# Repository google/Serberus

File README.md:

<h1 align="center">
  <br>
    <a>SERBERUS</a>
</h1>

<h4 align="center">Multi-headed and Multi-Protocol embedded system hacking tool.</h4>

<p align="center">
  
  <br>
</p>

# OVERVIEW
- Note: This is not an officially supported Google product
- The Serberus is a serial Man-in-the-Middle hardware hacking tool
- It has 4 channels, based on the FTDI 4233
- Has the ability to connect to JTAG, SPI, I2C and SWD interfaces
- Has a Level shifter and switch to allow you to connect to logic voltages of 1.8, 2.5 and 3.3v or any arbitrary voltage between 1.65v and 5.5v

# BOARD RENDERING 

<p align="center">
  
  <br>
</p>

# CONTENTS
- [System Requirements](#system-requirements)
- [What makes the Serberus unique](#what-makes-the-serberus-unique)
- [Basic Usage](#basic-usage)
  - [UARTS](#uarts)
  - [JTAG](#jtag)
  - [Other Connections](#swd-i2c-spi)
- [Switch 1](#switch-1)
- [Switch 2](#switch-2)
- [Jumpers](#jumpers-j8-and-j9)
  - [J8](#j8)
  - [J9](#j9)
- [UART]()
- [JTAG]()
- [SPI]()
- [I2C]()
- [Cortex](#cortex)
- [Logic Analyzer](#logic-analyzer)
- [Power Delivery](#power-delivery)
- [License](#license)

## System Requirements
No drivers should be required, the FTDI devices are supported by most operating systems.
The UART ports will work right away with screen, putty or your favorite serial console or serial access application such as OPENOCD.
## What makes the Serberus unique:
The Serberus is based on a couple of earlier FTDI USB to TTL tools, the TIMEP and the TIGARD. The items below are some of the major changes from those designs.
- 3 UART Ports
- J-Link Compatible JTAG connector - use any of those J-link to XXX connectors or breakouts
- Indicators for each of the 4 serial channels - help debugging
- 2.54 MM Logic Analyzer connector - Easily connect the most common logic analyzers or an MSO scope
## Basic Usage
When you plug in the Serberus, your system will be recognize the FTDI chip and the 4 serial ports. 
### UARTS
The first, third and forth serial ports are intended for UART. You can use your favorite serial access tool, (Putty, screen) to access them as you would any other USB to serial device
<br>
example<br>
`screen /dev/ttyUSB0 {baudrate}`

### JTAG
I need to do a little more work here as most of the tools like `pyftdi` and `flashrom` do not look for the FT4233. `pyftdi` should work with `--vidpid` flag and the value 0403:6041. You need to change udev permissions.
For OpenOCD, compile from source using "./configure --enable-ftdi". USB VID:PID is 0403:6041.

### SWD, I2C, SPI
Details coming soon

## SWITCH 1
Switch 1 is the rotary target voltage select switch, it has 4 positions. The first position is intended to match the voltage of your target and should rarely be needed, however it is included for those one-off scenarios where your target has a strange voltage between 1v6 and 5v5 but will not work with the provided levels. It will also adapt if your target changes voltage during the power up process. (I encountered this only once in all my years of testing.) J9 must have a jumper on it to make this connection.

The remaining 3 positions match the likely voltages of 1v8, 3v3 and 5v. Ideally in your workflow you will test your target and know what voltage level is appropriate. This switch works by taking the output of the voltage regulators U1, U2 or the 5v VBUS voltage and sending it to the level shifters VREF pin, to match the logic level of these signals.

| Position | Function |
|----------|----------|
| 1        | VTARGET  |
| 2        | 1v8      | 
| 3        | 3v3      |
| 4        | 5v       |

## SWITCH 2
Switch 2 is for combining various inputs to allow the second serial port to be used for JTAG, SPI, SWD and I2C. Switch to the left is for JTAG and SPI, separating the necessary TX and RX pins while the right position combines them for SWD and I2C.

## Jumpers J8 and J9
### J8 
connect VREF to VTARGET, allowing you to take the voltage level of your target and use that as the voltage level of the level shifters. J8 must have a jumper in place and SW1 must be in the first position for this feature to function.
### J9
For iCE FPGA programming, I added this feature from the TIGARD as it was an easy feature to include for a minimal cost. Close the jumper to connect UARTA_RX and Misc_RX, make sure SW2 is in JTAG mode. 

## UART
The top connector has 3 UART connections, it is a standard 20 pin flat cable connector. The first UART has all 7 signal pins connected, for those rare instances where they are needed. The first UART is mapped to the first 4233 channel.
<br>
The second and third UARTS are mapped to the 3rd and 4th channels ports, as the second is used by the combined JTAG/SWD/I2C and SPI port. These ports only have TX and RX connected.

### UART Header Pinout

| Pin   | Function  |
|-------|-----------|
| 1     | VTARGET   |
| 2     | VTARGET   | 
| 3     | GND       |
| 4     | TX-C      |
| 5     | TX-A      |
| 6     | RX-C      |
| 7     | RX-A      |
| 8     | GND       |
| 9     | RTS-A     |
| 10    | NC        |
| 11    | CTS-A     |
| 12    | RX-D      |
| 13    | DTR-A     |
| 14    | VTARGET   |
| 15    | DSR-A     |
| 16    | TX-D      |
| 17    | DCD-A     |
| 18    | RX-D      |
| 19    | NC        |
| 20    | GND       |

## JTAG
The JTAG header is presented on J3, the right side of the board opposite the USB connector. The connector is a 20 Pin standard pitch Flat cable style.  It is intended to match the Segger J-LINK pinout as much as possible, making it easier to use the many J-Link connectors to make a direct connection to an accessible header on your target.

### JTAG Header Pinout

| Pin   | Function |
|-------|----------|
| 1     | VTARGET  |
| 2     | NC       |
| 3     | TRST     |
| 4     | GND      |
| 5     | TDI      |
| 6     | GND      |
| 7     | TMS      |
| 8     | GND      |
| 9     | TCK      |
| 10    | GND      |
| 11    | MISC_RX* |
| 12    | GND      | 
| 13    | TDO      | 
| 14    | GND      |
| 15    | SRST     |
| 16    | GND      |
| 17    | NC       |
| 18    | GND      |
| 19    | NC       |
| 20    | GND      |

*Connected to BDBUS 6 as an input on the FT4233, only needed for bizarre on-off connections, for most purposes, leave as NC.

## SPI
 SW2 in _leftmost_ position (1)
### SPI Pinout:
| Pin   | Function      |
|-------|---------------|
| 1     | CS            |
| 2     | VTARGET       |
| 3     | CIPO/MISO     |
| 4     | WP (PULLUP)   |
| 5     | EN (PULLUP)   |
| 6     | CLK           |
| 7     | GND           |
| 8     | COPI/MOSI     |

## I2C
 SW2 in _rightmost_ position (2)
### I2C Pinout:
| Pin   | Function |
|-------|----------|
| 1     | SCL      |
| 2     | SDA      |
| 3     | VTARGET  |
| 4     | GND      |

## CORTEX
A 10 pin cortex debug connector is present and will enable an easy connection to this common debug connector. 
### CORTEX Pinout
| Pin   | Function     |
|-------|--------------|
| 1     | VTARGET      |
| 2     | CORTEX PIN 2 |
| 3     | GND          |
| 4     | TCK          |
| 5     | GND          |
| 6     | TDO          |
| 7     | NC           |
| 8     | TDI          |
| 9     | GND          |
| 10    | SRST         |

## Logic Analyzer
The 14 pin header at the bottom next to the SPI and I2C connectors replicates most of the signal lines for easy connection to a logic analyzer or digital MSO lines of an oscilloscope. The pin header is standard 2.54mm pitch to easily connect using standard Dupont style jumper wires.
### Logic Analyzer Pinout

| Pin   | Function      |
|-------|---------------|
| 1     | CLK           |
| 2     | COPI/TDI      | 
| 3     | CIPO/TDO/SWDIO|
| 4     | TMS/CS        |
| 5     | TRST          |
| 6     | SRST          |
| 7     | TX-A          |
| 8     | RX-A          |
| 9     | TX-C          |
| 10    | RX-C          |
| 11    | TX-D          |
| 12    | RX-D          |
| 13    | GND           |
| 14    | GND           |

## POWER DELIVERY
The FT4233 is capable of power delivery (PD) and the design includes a DPO2036 for OVP. No other PD features have been added and the FTDI settings are at default. Power delivery is something that could be added but is well beyond the scope of this device for its initial release. Please feel free to experiment with forked designs.

## License
```Copyright 2024 Google LLC
Licensed under the Apache License, Version 2.0 (the "License");
you may not use this file except in compliance with the License.
You may obtain a copy of the License at

    https://www.apache.org/licenses/LICENSE-2.0

Unless required by applicable law or agreed to in writing, software
distributed under the License is distributed on an "AS IS" BASIS,
WITHOUT WARRANTIES OR CONDITIONS OF ANY KIND, either express or implied.
See the License for the specific language governing permissions and
limitations under the License.
```

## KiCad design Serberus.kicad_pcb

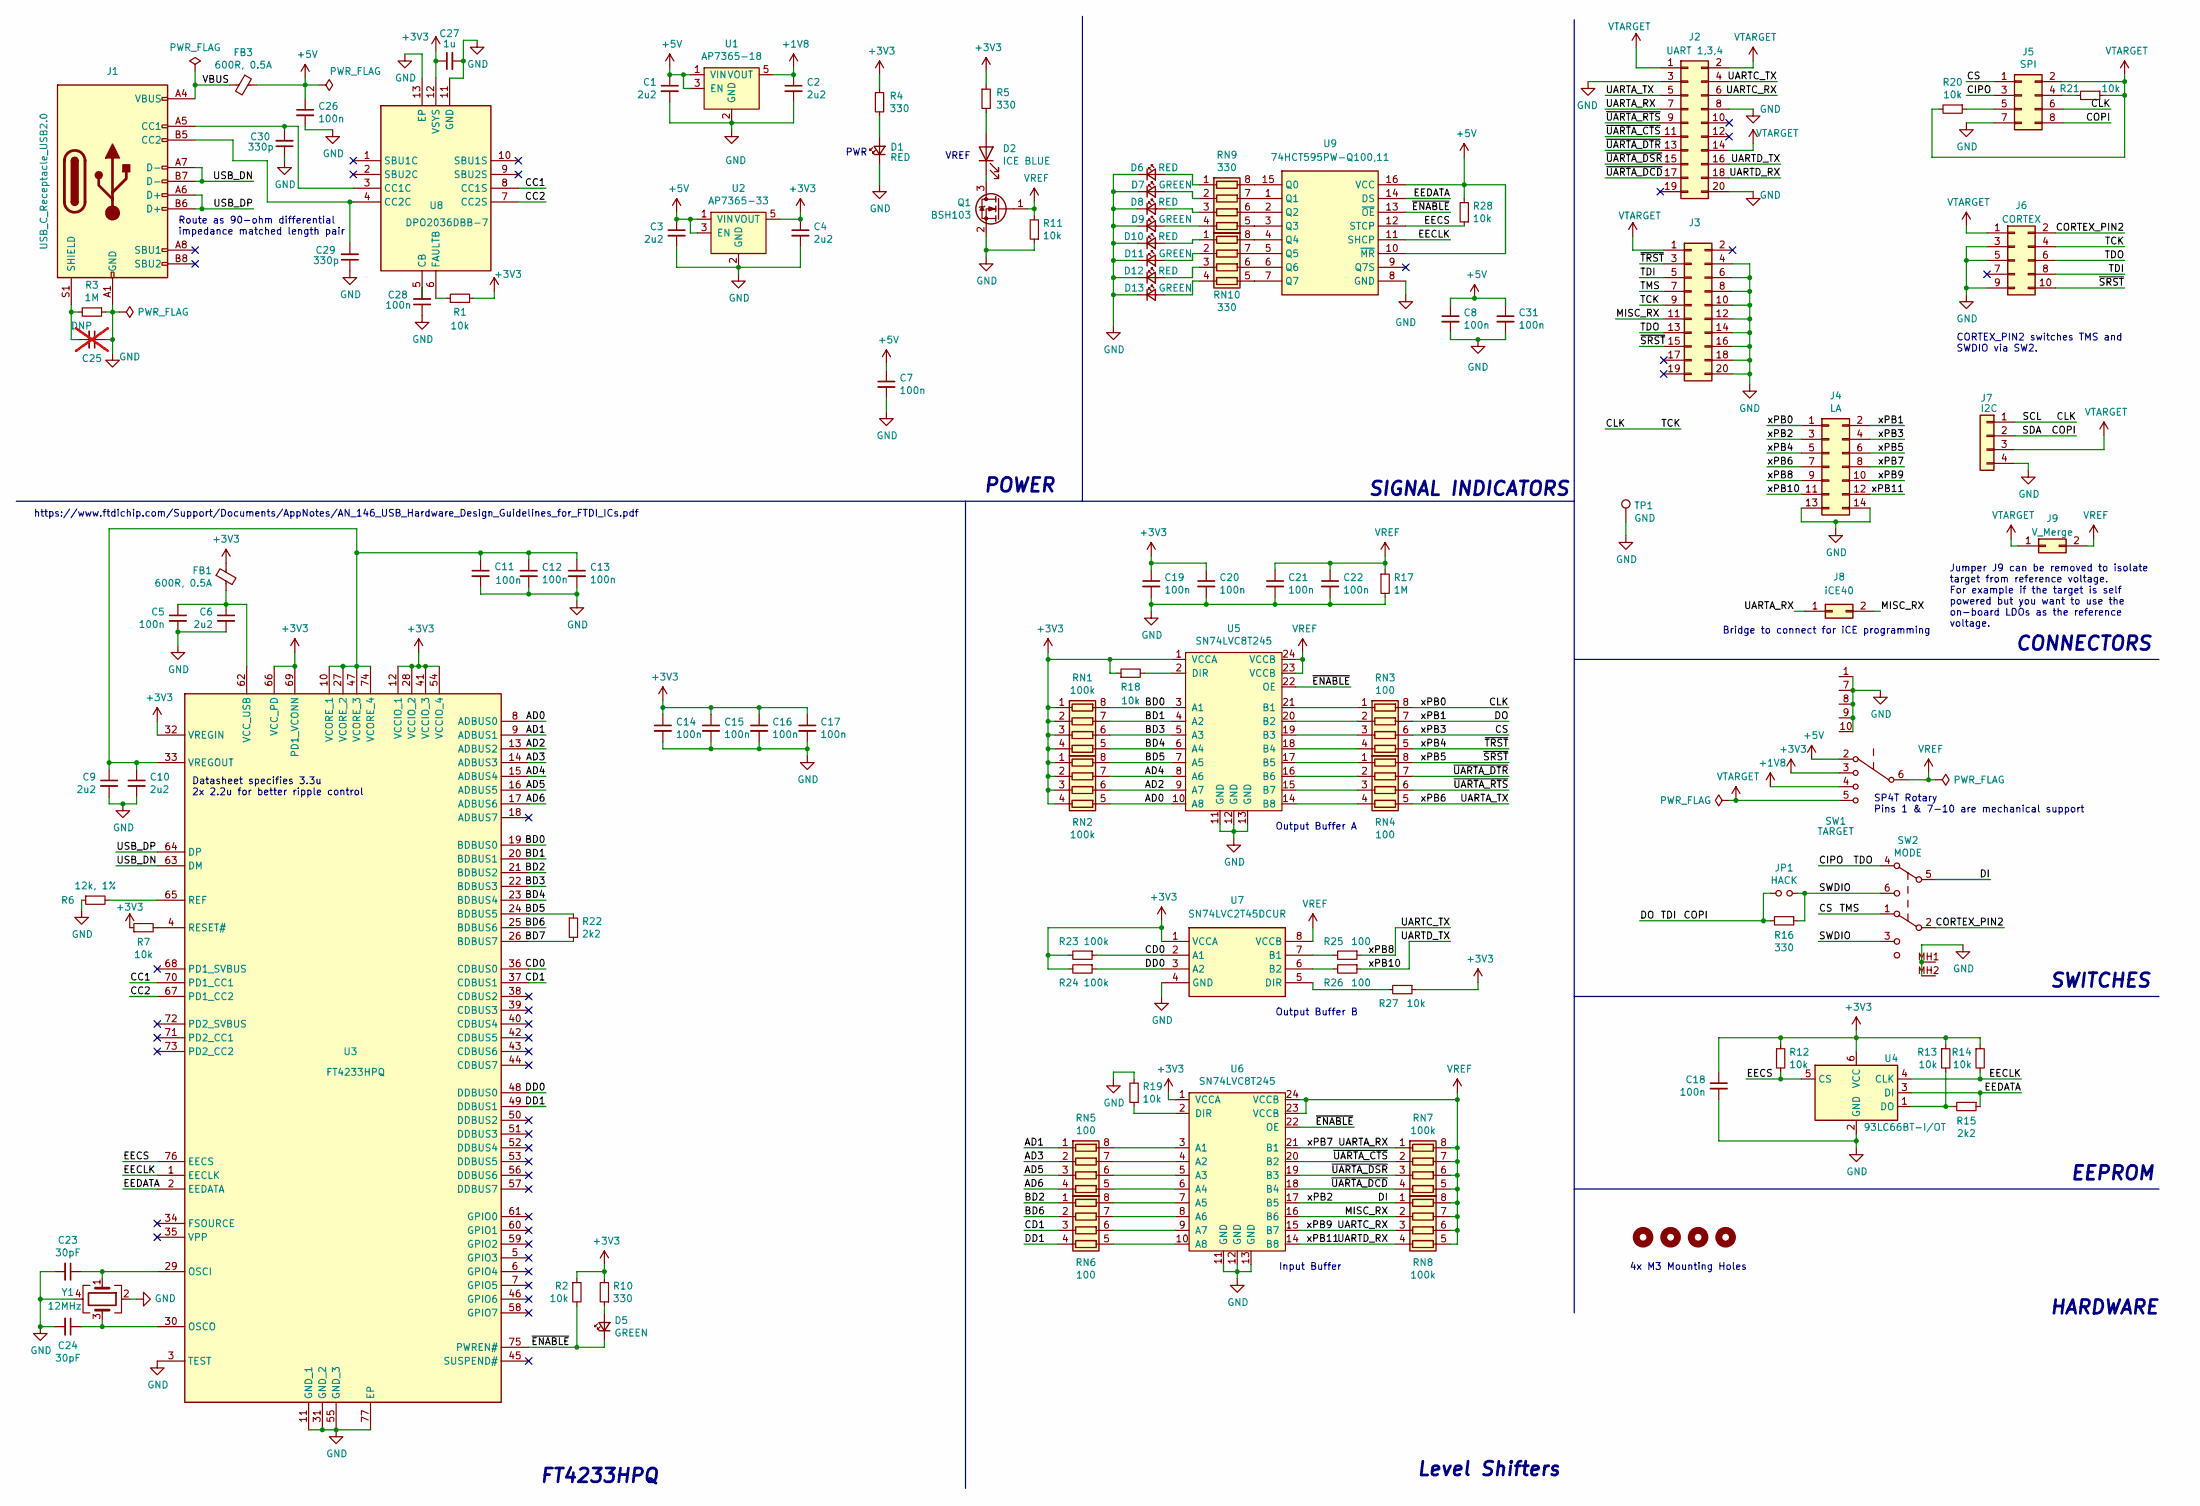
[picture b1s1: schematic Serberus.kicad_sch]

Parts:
C1, C2, C3, C4, C6, C9, C10: 2u2; C_0402_1005Metric; LCSC C307419
C5, C7, C8, C11, C12, C13, C14, C15, C16, C17, C18, C19, C20, C21, C22, C26, C28, C31: 100n; C_0402_1005Metric; LCSC C100072
C23, C24: 30pF; C_0402_1005Metric; LCSC C159804
C25: DNP; C_0402_1005Metric; not fitted
C27: 1u; C_0402_1005Metric; LCSC C52923
C29, C30: 330p; C_0402_1005Metric; LCSC C307432
D1, D6, D8, D10, D12: RED; LED_0603_1608Metric; LCSC C157741
D2: ICE BLUE; LED_0603_1608Metric; LCSC C389522
D5, D7, D9, D11, D13: GREEN; LED_0603_1608Metric; LCSC C12065
FB1, FB3: 600R, 0.5A; L_0402_1005Metric; LCSC C76886
H1, H2, H3, H4: MountingHole; MountingHole_3.2mm_M3_ISO7380
J1: USB_C_Receptacle_USB2.0; USB_C_Receptacle_HRO_TYPE-C-31-M-12; LCSC C165948
J2: UART 1,3,4; RHDRRA20W64P254_2X10_3306X885X910P; Mouser Part Number 571-5103311-5
J3: SWD/JTAG2; RHDRRA20W64P254_2X10_3306X885X910P; Mouser Part Number 571-5103311-5
J4: LA; PinHeader_2x07_P2.54mm_Vertical; LCSC C5156678
J5: SPI; PinHeader_2x04_P2.54mm_Vertical; LCSC C492421
J6: CORTEX; PinHeader_2x05_P1.27mm_Vertical_SMD; LCSC C448647
J7: I2C; PinHeader_1x04_P2.54mm_Vertical; LCSC C2691448
J8: iCE40; PinHeader_1x02_P2.54mm_Vertical; LCSC C492401
J9: V_Merge; PinHeader_1x02_P2.54mm_Vertical; LCSC C492401
JP1: HACK; SolderJumper-2_P1.3mm_Open_RoundedPad1.0x1.5mm
Q1: BSH103; SOT-23_RoundRect; LCSC C88711
R1, R2, R7, R11, R12, R13, R14, R18, R19, R20, R21, R27, R28: 10k; R_0402_1005Metric; LCSC C25744
R3, R17: 1M; R_0402_1005Metric; LCSC C26087
R4, R5, R10, R16: 330; R_0402_1005Metric; LCSC C25104
R6: 12k, 1%; R_0402_1005Metric; LCSC C25752
R15, R22: 2k2; R_0402_1005Metric; LCSC C25879
R23, R24: 100k; R_0402_1005Metric; LCSC C25741
R25: 100; R_0402_1005Metric; LCSC C25076
R26: 100; R_0402_1005Metric; LCSC C25879
RN1, RN2, RN7, RN8: 100k; R_Array_Convex_4x0402_RoundRect; LCSC C25724
RN3, RN4, RN5, RN6: 100; R_Array_Convex_4x0402_RoundRect; LCSC C48442
RN9, RN10: 330; R_Array_Convex_4x0402_RoundRect; LCSC C43557
SW1: TARGET; NR01105ANG132A; Manufacturer_Part_Number NR01105ANG13-2A; Mouser Part Number 633-NR01105ANG13-2A
SW2: MODE; SSSF021500; Mouser Part Number 688-SSSF021500
TP1: GND; TestPoint_Keystone_5000-5004_Miniature; LCSC C238122
U1: AP7365-18; SOT-23-5_RoundRect; LCSC C460402
U2: AP7365-33; SOT-23-5_RoundRect; LCSC C150742
U3: FT4233HPQ; QFN40P900X900X100-77N-D; Mouser Part Number 895-FT4233HPQ-TRAY
U4: 93LC66BT-I/OT; SOT-23-6_RoundRect; LCSC C2061454
U5, U6: SN74LVC8T245; TSSOP-24_4.4x7.8mm_P0.65mm; LCSC C27643
U7: SN74LVC2T45DCUR; SOP50P310X90-8N; Mouser Part Number 595-SN74LVC2T45DCUR
U8: DPO2036DBB-7; QFN45P200X200X65-13N; Mouser Part Number 621-DPO2036DBB-7
U9: 74HCT595PW-Q100,11; SOP65P640X110-16N; Mouser Part Number 771-74HCT595PWQ10011
Y1: 12MHz; Crystal_SMD_3225-4Pin_3.2x2.5mm_RoundRect; LCSC C9002

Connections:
+1V8: C2.1, SW1.4, U1.5 (VOUT)
+3V3: C4.1, C14.1, C15.1, C16.1, C17.1, C18.1, C19.1, C20.1, C27.1, FB1.1, R1.2, R2.1, R4.1, R5.1, R7.1, R10.2, R12.1, R13.1, R14.1, R18.1, R23.2, R24.2, R27.1, RN1.1 (R1.1), RN1.2 (R2.1), RN1.3 (R3.1), RN1.4 (R4.1), RN2.1 (R1.1), RN2.2 (R2.1), RN2.3 (R3.1), RN2.4 (R4.1), SW1.3, U2.5 (VOUT), U3.12 (VCCIO_1), U3.28 (VCCIO_2), U3.32 (VREGIN), U3.41 (VCCIO_3), U3.54 (VCCIO_4), U3.66 (VCC_PD), U3.69 (PD1_VCONN), U4.6 (VCC), U5.1 (VCCA), U6.1 (VCCA), U7.1 (VCCA), U8.12 (VSYS)
+5V: C1.1, C3.1, C7.1, C8.1, C26.1, C31.1, FB3.1, R28.2, SW1.2, U1.1 (VIN), U1.3 (EN), U2.1 (VIN), U2.3 (EN), U9.10 (~MR), U9.16 (VCC)
/AD0: RN2.5 (R4.2), U3.8 (ADBUS0), U5.10 (A8)
/AD1: RN5.1 (R1.1), U3.9 (ADBUS1)
/AD2: RN2.6 (R3.2), U3.13 (ADBUS2), U5.9 (A7)
/AD3: RN5.2 (R2.1), U3.14 (ADBUS3)
/AD4: RN2.7 (R2.2), U3.15 (ADBUS4), U5.8 (A6)
/AD5: RN5.3 (R3.1), U3.16 (ADBUS5)
/AD6: RN5.4 (R4.1), U3.17 (ADBUS6)
/BD0: RN1.8 (R1.2), U3.19 (BDBUS0), U5.3 (A1)
/BD1: RN1.7 (R2.2), U3.20 (BDBUS1), U5.4 (A2)
/BD2: RN6.1 (R1.1), U3.21 (BDBUS2)
/BD3: RN1.6 (R3.2), U3.22 (BDBUS3), U5.5 (A3)
/BD4: RN1.5 (R4.2), U3.23 (BDBUS4), U5.6 (A4)
/BD5: R22.1, RN2.8 (R1.2), U3.24 (BDBUS5), U5.7 (A5)
/BD6: RN6.2 (R2.1), U3.25 (BDBUS6)
/BD7: R22.2, U3.26 (BDBUS7)
/CC1: U3.70 (PD1_CC1), U8.8 (CC1S)
/CC2: U3.67 (PD1_CC2), U8.7 (CC2S)
/CD0: R23.1, U3.36 (CDBUS0), U7.2 (A1)
/CD1: RN6.3 (R3.1), U3.37 (CDBUS1)
/CIPO: J3.13, J5.3, J6.6, SW2.4
/CLK: J3.9, J4.1, J5.6, J6.4, J7.1, RN3.8 (R1.2)
/COPI: J3.5, J4.2, J5.8, J6.8, J7.2, JP1.1, R16.2, RN3.7 (R2.2)
/CORTEX_PIN2: J6.2, SW2.2
/CS: J3.7, J4.4, J5.1, RN3.6 (R3.2), SW2.1
/DD0: R24.1, U3.48 (DDBUS0), U7.3 (A2)
/DD1: RN6.4 (R4.1), U3.49 (DDBUS1)
/DI: J4.3, RN8.1 (R1.1), SW2.5, U6.17 (B5)
/EECLK: R14.2, U3.1 (EECLK), U4.4 (CLK), U9.11 (SHCP)
/EECS: R12.2, R28.1, U3.76 (EECS), U4.5 (CS), U9.12 (STCP)
/EEDATA: R15.1, U3.2 (EEDATA), U4.3 (DI), U9.14 (DS)
/MISC_RX: J3.11, J8.2, RN8.2 (R2.1), U6.16 (B6)
/SWDIO: JP1.2, R16.1, SW2.3, SW2.6
/UARTA_RX: J2.7, J4.8, J8.1, RN7.1 (R1.1), U6.21 (B1)
/UARTA_TX: J2.5, J4.7, RN4.5 (R4.2)
/UARTC_RX: J2.6, J4.10, RN8.3 (R3.1), U6.15 (B7)
/UARTC_TX: J2.4, J4.9, R25.1
/UARTD_RX: J2.18, J4.12, RN8.4 (R4.1), U6.14 (B8)
/UARTD_TX: J2.16, J4.11, R26.1
/USB_DN: J1.A7 (D-), J1.B7 (D-), U3.63 (DM)
/USB_DP: J1.A6 (D+), J1.B6 (D+), U3.64 (DP)
/VBUS: FB3.2, J1.A4 (VBUS), J1.A9 (VBUS), J1.B4 (VBUS), J1.B9 (VBUS)
/xPB4: J3.3, J4.5, RN3.5 (R4.2)
/xPB5: J3.15, J4.6, J6.10, RN4.8 (R1.2)
/~ENABLE: D5.1 (K), R2.2, U3.75 (PWREN#), U5.22 (OE), U6.22 (OE), U9.13 (~OE)
/~UARTA_CTS: J2.11, RN7.2 (R2.1), U6.20 (B2)
/~UARTA_DCD: J2.17, RN7.4 (R4.1), U6.18 (B4)
/~UARTA_DSR: J2.15, RN7.3 (R3.1), U6.19 (B3)
/~UARTA_DTR: J2.13, RN4.7 (R2.2)
/~UARTA_RTS: J2.9, RN4.6 (R3.2)
GND: C1.2, C2.2, C3.2, C4.2, C5.2, C6.2, C7.2, C8.2, C9.2, C10.2, C11.2, C12.2, C13.2, C14.2, C15.2, C16.2, C17.2, C18.2, C19.2, C20.2, C21.2, C22.2, C23.2, C24.2, C25.1, C26.2, C27.2, C28.1, C29.1, C30.1, C31.2, D1.1 (K), D6.1 (K), D7.1 (K), D8.1 (K), D9.1 (K), D10.1 (K), D11.1 (K), D12.1 (K), D13.1 (K), J1.A1 (GND), J1.A12 (GND), J1.B1 (GND), J1.B12 (GND), J2.3, J2.8, J2.20, J3.4, J3.6, J3.8, J3.10, J3.12, J3.14, J3.16, J3.18, J3.20, J4.13, J4.14, J5.7, J6.3, J6.5, J6.9, J7.4, Q1.2 (S), R3.1, R6.1, R11.1, R17.2, R19.2, SW1.1 (1_Support), SW1.7 (7_Support), SW1.8 (8_Support), SW1.9 (9_Support), SW1.10 (10_Support), SW2.MH1, SW2.MH2, TP1.1, U1.2 (GND), U2.2 (GND), U3.3 (TEST), U3.11 (GND_1), U3.31 (GND_2), U3.55 (GND_3), U3.77 (EP), U4.2 (GND), U5.11 (GND), U5.12 (GND), U5.13 (GND), U6.11 (GND), U6.12 (GND), U6.13 (GND), U7.4 (GND), U8.11 (GND), U8.13 (EP), U9.8 (GND), Y1.2, Y1.4
unnamed: D1.2 (A), R4.2
unnamed: D2.2 (A), R5.2
unnamed: D2.1 (K), Q1.3 (D)
unnamed: D5.2 (A), R10.1
unnamed: D6.2 (A), RN9.1 (R1.1)
unnamed: D7.2 (A), RN9.2 (R2.1)
unnamed: D8.2 (A), RN9.3 (R3.1)
unnamed: D9.2 (A), RN9.4 (R4.1)
unnamed: D10.2 (A), RN10.1 (R1.1)
unnamed: D11.2 (A), RN10.2 (R2.1)
unnamed: D12.2 (A), RN10.3 (R3.1)
unnamed: D13.2 (A), RN10.4 (R4.1)
unnamed: C30.2, J1.A5 (CC1), U8.3 (CC1C)
unnamed: C29.2, J1.B5 (CC2), U8.4 (CC2C)
unnamed: C25.2, J1.S1 (SHIELD), R3.2
unnamed: J5.4, R21.2
unnamed: J5.5, R20.1
unnamed: RN3.1 (R1.1), U5.21 (B1)
unnamed: RN3.2 (R2.1), U5.20 (B2)
unnamed: RN3.3 (R3.1), U5.19 (B3)
unnamed: RN3.4 (R4.1), U5.18 (B4)
unnamed: RN4.1 (R1.1), U5.17 (B5)
unnamed: RN4.2 (R2.1), U5.16 (B6)
unnamed: RN4.3 (R3.1), U5.15 (B7)
unnamed: RN4.4 (R4.1), U5.14 (B8)
unnamed: RN5.8 (R1.2), U6.3 (A1)
unnamed: RN5.7 (R2.2), U6.4 (A2)
unnamed: RN5.6 (R3.2), U6.5 (A3)
unnamed: RN5.5 (R4.2), U6.6 (A4)
unnamed: RN6.8 (R1.2), U6.7 (A5)
unnamed: RN6.7 (R2.2), U6.8 (A6)
unnamed: RN6.6 (R3.2), U6.9 (A7)
unnamed: RN6.5 (R4.2), U6.10 (A8)
unnamed: RN9.8 (R1.2), U9.15 (Q0)
unnamed: RN9.7 (R2.2), U9.1 (Q1)
unnamed: RN9.6 (R3.2), U9.2 (Q2)
unnamed: RN9.5 (R4.2), U9.3 (Q3)
unnamed: RN10.8 (R1.2), U9.4 (Q4)
unnamed: RN10.7 (R2.2), U9.5 (Q5)
unnamed: RN10.6 (R3.2), U9.6 (Q6)
unnamed: RN10.5 (R4.2), U9.7 (Q7)
unnamed: C23.1, U3.29 (OSCI), Y1.1
unnamed: C24.1, U3.30 (OSCO), Y1.3
unnamed: R6.2, U3.65 (REF)
unnamed: R7.2, U3.4 (RESET#)
unnamed: C5.1, C6.1, FB1.2, U3.62 (VCC_USB)
unnamed: C9.1, C10.1, C11.1, C12.1, C13.1, U3.10 (VCORE_1), U3.27 (VCORE_2), U3.33 (VREGOUT), U3.47 (VCORE_3), U3.74 (VCORE_4)
unnamed: R13.2, R15.2, U4.1 (DO)
unnamed: R18.2, U5.2 (DIR)
unnamed: R19.1, U6.2 (DIR)
unnamed: R25.2, U7.7 (B1)
unnamed: R26.2, U7.6 (B2)
unnamed: R27.2, U7.5 (DIR)
unnamed: C28.2, U8.5 (CB)
unnamed: R1.1, U8.6 (FAULTB)
VREF: C21.1, C22.1, J9.2, Q1.1 (G), R11.2, R17.1, RN7.5 (R4.2), RN7.6 (R3.2), RN7.7 (R2.2), RN7.8 (R1.2), RN8.5 (R4.2), RN8.6 (R3.2), RN8.7 (R2.2), RN8.8 (R1.2), SW1.6 (Common), U5.23 (VCCB), U5.24 (VCCB), U6.23 (VCCB), U6.24 (VCCB), U7.8 (VCCB)
VTARGET: J2.1, J2.2, J2.14, J3.1, J5.2, J6.1, J7.3, J9.1, R20.2, R21.1, SW1.5

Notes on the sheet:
Datasheet specifies 3.3u 2x 2.2u for better ripple control
SWITCHES
EEPROM
SIGNAL INDICATORS
Route as 90-ohm differential impedance matched length pair
Level Shifters
VREF
FT4233HPQ
HARDWARE
Output Buffer B
https://www.ftdichip.com/Support/Documents/AppNotes/AN_146_USB_Hardware_Design_Guidelines_for_FTDI_ICs.pdf
Output Buffer A
SP4T Rotary Pins 1 & 7-10 are mechanical support
4x M3 Mounting Holes
Input Buffer
PWR
POWER
Bridge to connect for iCE programming
CORTEX_PIN2 switches TMS and SWDIO via SW2.
Jumper J9 can be removed to isolate target from reference voltage. For example if the target is self powered but you want to use the on-board LDOs as the reference voltage.
CONNECTORS

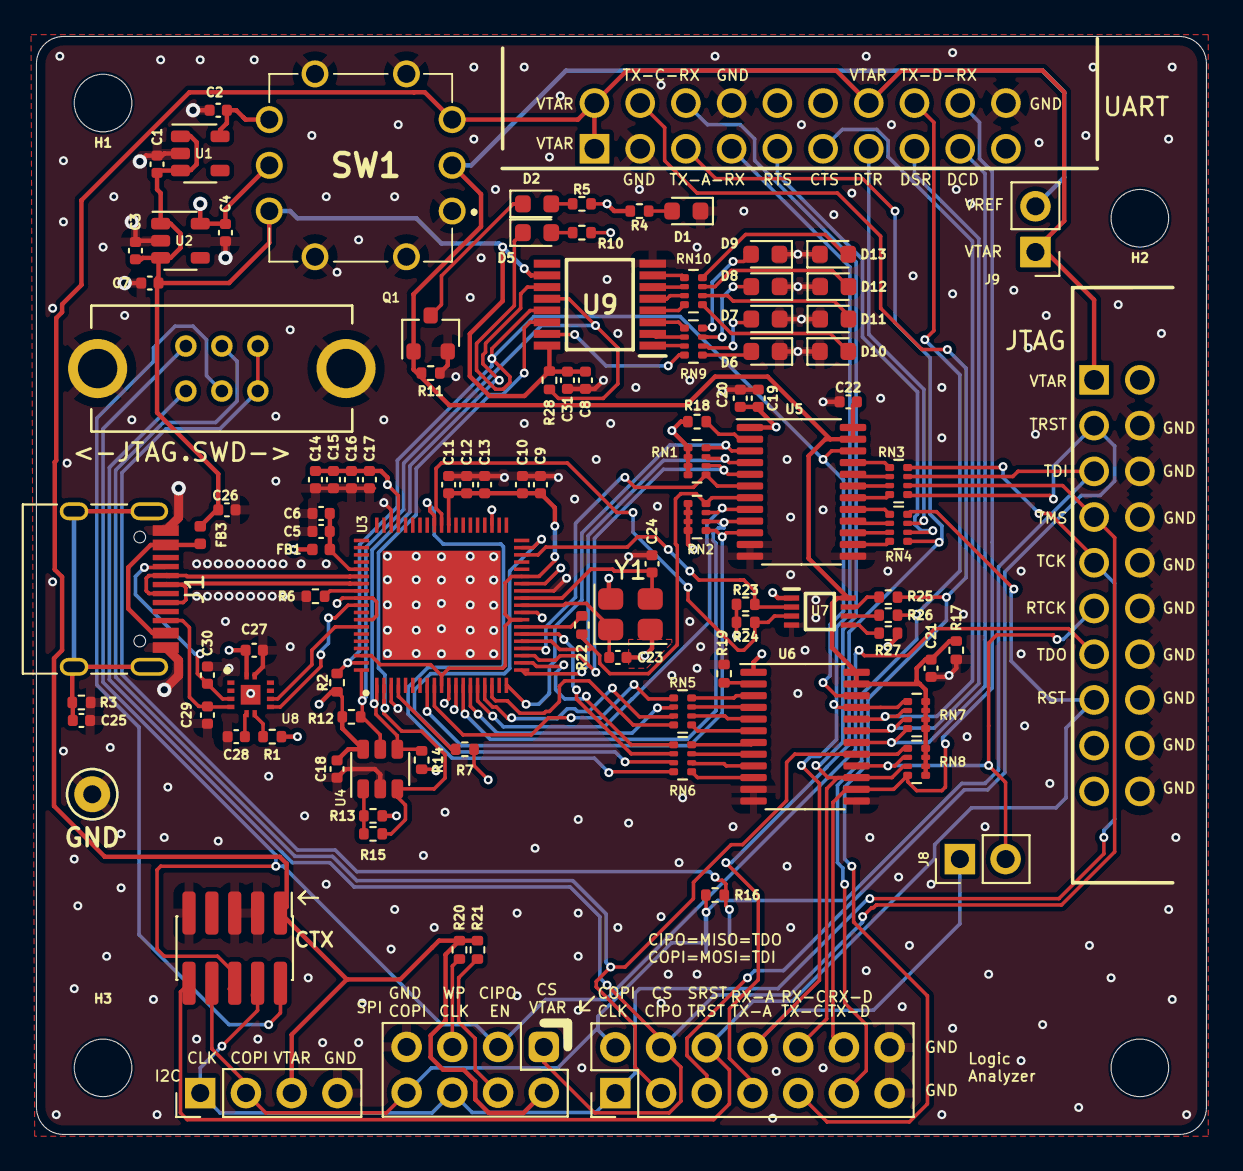
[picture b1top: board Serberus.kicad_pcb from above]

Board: 4 copper layers, 65.0 x 61.0 mm, 108 parts (1 on the bottom side), 110 nets.

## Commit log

2024-07-29 Update Serberus.kicad_sch
    Updated part numbers
2025-08-20 Update README.md
    Added JTAG OpenOCD documentation.

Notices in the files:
Serberus.kicad_pcb:
Licensed under Apache 2.0
Serberus.kicad_sch:
Apache-2.0 Open Source License
